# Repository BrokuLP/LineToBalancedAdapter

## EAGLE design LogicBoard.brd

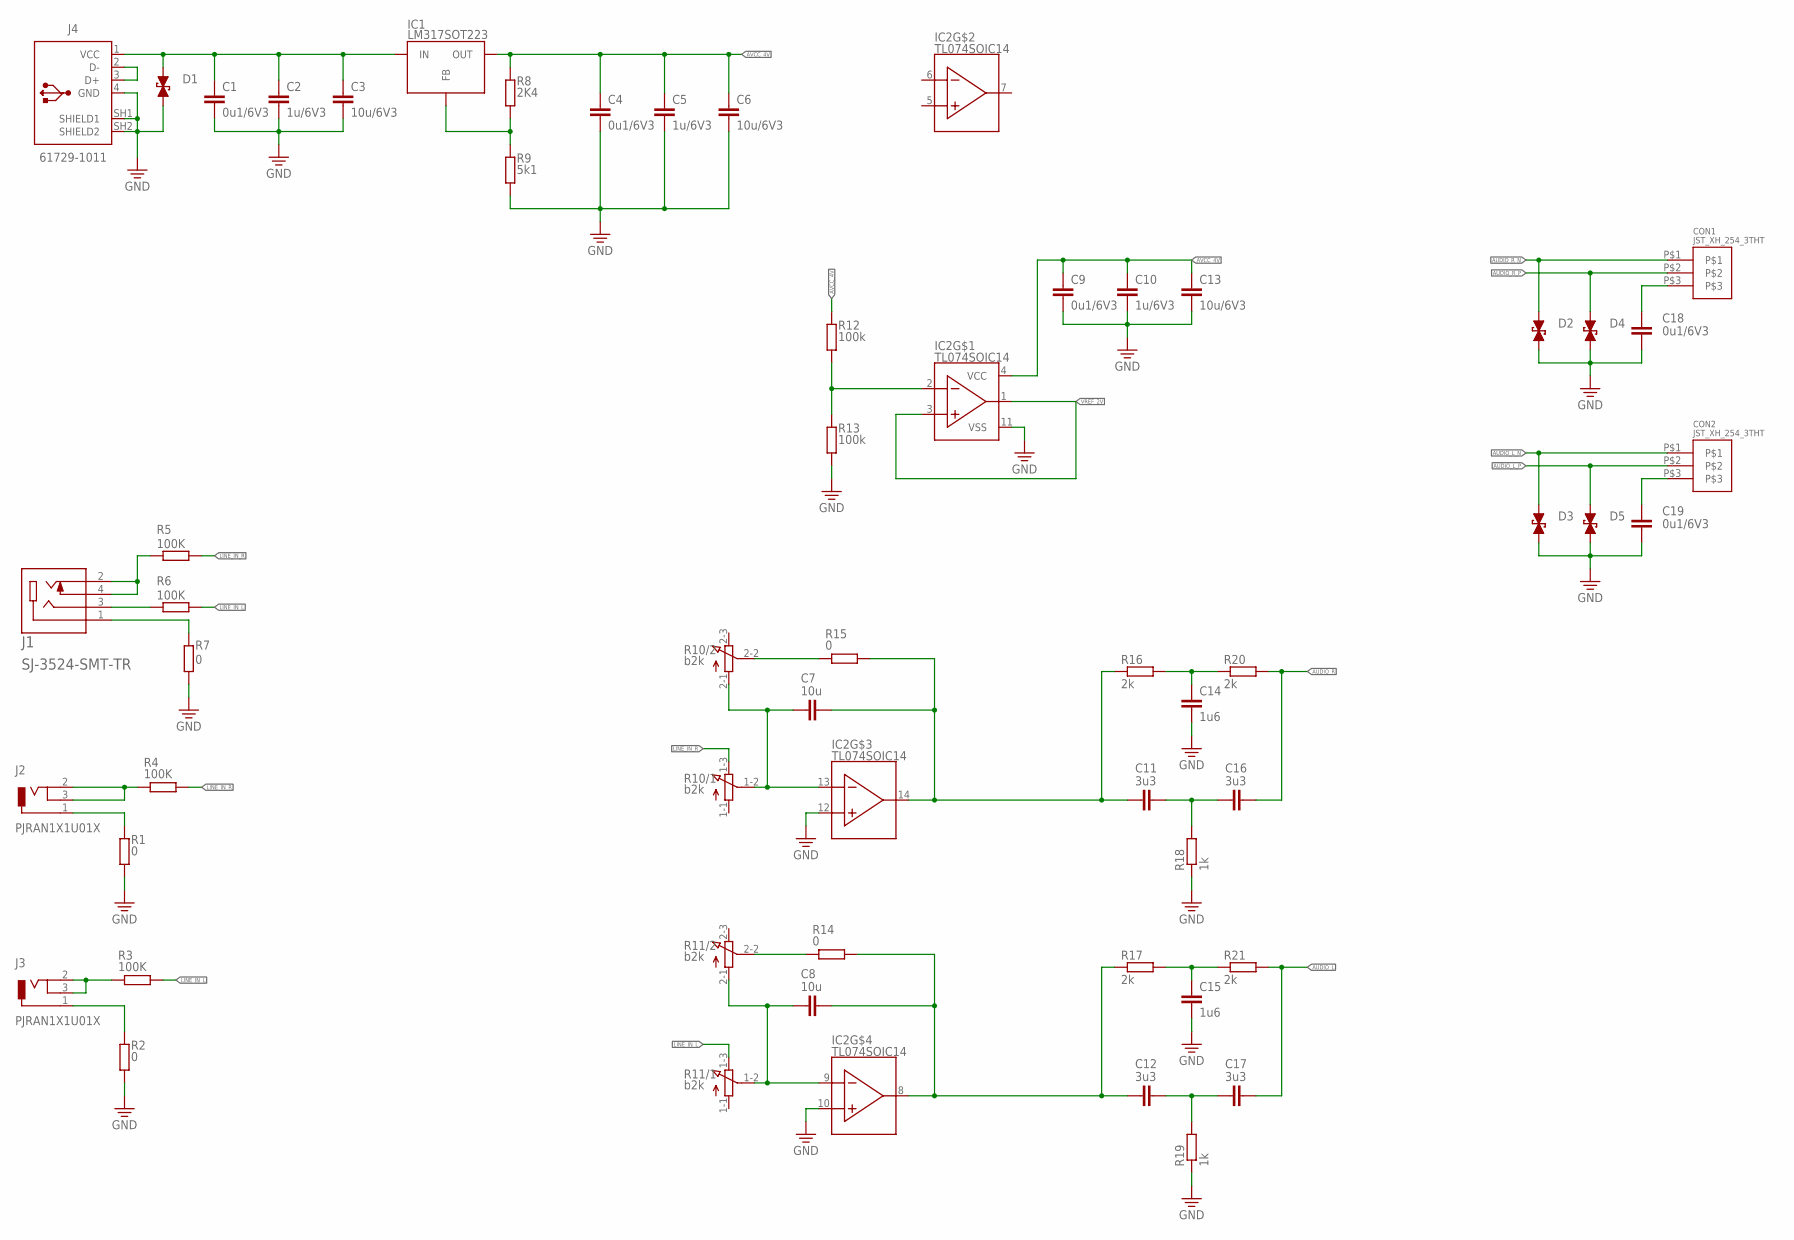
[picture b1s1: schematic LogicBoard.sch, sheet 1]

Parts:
C1, C4, C9, C18, C19: 0u1/6V3; C1206
C2, C5, C10: 1u/6V3; C1206
C3, C6, C13: 10u/6V3; C1206
C7, C8: 10u; C1206
C11, C12, C16, C17: 3u3; C1206
C14, C15: 1u6; C1206
CON1, CON2: JST_XH_254_3THT; JST_XH_254_3_THT
D1, D2, D3, D4, D5: DIODE_PGB-0603MP
IC1: LM317SOT223; SOT230P700X180-4N
IC2: TL074SOIC14; SOIC127P600X175-14N
J1: SJ-3524-SMT-TR
J2, J3: PJRAN1X1U01X
J4: 61729-1011; 61729-1011BLF
R1, R2, R7, R14, R15: 0; R0603
R3, R4, R5, R6: 100K; R0603
R8: 2K4; R0603
R9: 5k1; R0603
R10, R11: b2k; 3RP/1610G
R12, R13: 100k; R0603
R16, R17, R20, R21: 2k; R0603
R18, R19: 1k; R0603

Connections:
AUDIO_L: C17.2, R21.2; also elsewhere on the board
AUDIO_L_N: CON2.P$1, D3.2; also elsewhere on the board
AUDIO_L_P: CON2.P$2, D5.2; also elsewhere on the board
AUDIO_R: C16.2, R20.2; also elsewhere on the board
AUDIO_R_N: CON1.P$1, D2.2; also elsewhere on the board
AUDIO_R_P: CON1.P$2, D4.2; also elsewhere on the board
AVCC_4V: C4.1, C5.1, C6.1, C9.1, C10.1, C13.1, IC1.2 (OUT), IC2.4 (VCC), R8.2, R12.2; also elsewhere on the board
GND: C1.2, C2.2, C3.2, C4.2, C5.2, C6.2, C9.2, C10.2, C13.2, C14.2, C15.2, C18.1, C19.1, D1.1, D2.1, D3.1, D4.1, D5.1, IC2.10 (IN+), IC2.11 (VSS), IC2.12 (IN+), J4.4 (GND), J4.SH1 (SHIELD1), J4.SH2 (SHIELD2), R1.2, R2.2, R7.2, R9.1, R13.1, R18.1, R19.1; also elsewhere on the board
L: J1.3, R6.1
LINE_IN_L: R3.2, R6.2, R11.1-3 (E)
LINE_IN_R: R4.2, R5.2, R10.1-3 (E)
unnamed: C8.1, IC2.9 (IN-), R11.1-2 (S), R11.2-1 (A)
unnamed: C7.1, IC2.13 (IN-), R10.1-2 (S), R10.2-1 (A)
unnamed: C8.2, C12.1, IC2.8 (OUT), R14.2, R17.1
unnamed: C7.2, C11.1, IC2.14 (OUT), R15.2, R16.1
unnamed: C14.1, R16.2, R20.1
unnamed: R10.2-2 (S), R15.1
unnamed: C15.1, R17.2, R21.1
unnamed: C11.2, C16.1, R18.2
unnamed: C12.2, C17.1, R19.2
unnamed: J2.2, J2.3, R4.1
unnamed: J3.2, J3.3, R3.1
unnamed: IC2.2 (IN-), R12.1, R13.2
unnamed: C18.2, CON1.P$3
unnamed: J4.2 (D-), J4.3 (D+)
unnamed: J3.1, R2.1
unnamed: J2.1, R1.1
unnamed: C1.1, C2.1, C3.1, D1.2, IC1.3 (IN), J4.1 (VCC)
unnamed: R11.2-2 (S), R14.1
unnamed: IC1.1 (FB), R8.1, R9.2
unnamed: C19.2, CON2.P$3
R: J1.2, J1.4, R5.1
SCHIRMUNG: J1.1, R7.1
VREF_2V: IC2.1 (OUT), IC2.3 (IN+); also elsewhere on the board

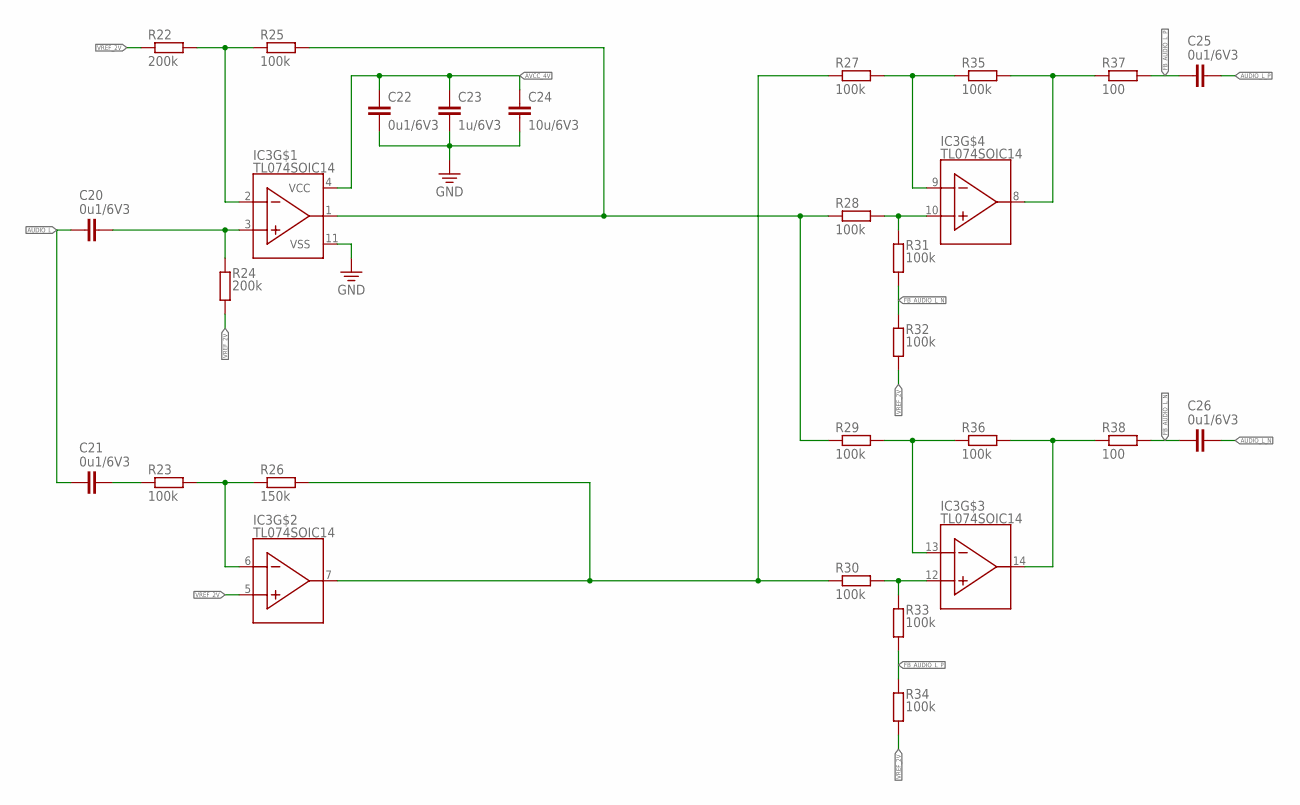
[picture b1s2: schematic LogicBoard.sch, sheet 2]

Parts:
C20, C21, C22, C25, C26: 0u1/6V3; C1206
C23: 1u/6V3; C1206
C24: 10u/6V3; C1206
IC3: TL074SOIC14; SOIC127P600X175-14N
R22, R24: 200k; R0603
R23, R25, R27, R28, R29, R30, R31, R32, R33, R34, R35, R36: 100k; R0603
R26: 150k; R0603
R37, R38: 100; R0603

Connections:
AUDIO_L: C20.2, C21.2; also elsewhere on the board
AUDIO_L_N: C26.1; also elsewhere on the board
AUDIO_L_P: C25.1; also elsewhere on the board
AVCC_4V: C22.1, C23.1, C24.1, IC3.4 (VCC); also elsewhere on the board
FB_AUDIO_L_N: C26.2, R31.2, R32.1, R38.2
FB_AUDIO_L_P: C25.2, R33.2, R34.1, R37.2
GND: C22.2, C23.2, C24.2, IC3.11 (VSS); also elsewhere on the board
unnamed: IC3.6 (IN-), R23.2, R26.1
unnamed: IC3.2 (IN-), R22.2, R25.1
unnamed: IC3.9 (IN-), R27.2, R35.1
unnamed: IC3.8 (OUT), R35.2, R37.1
unnamed: IC3.10 (IN+), R28.2, R31.1
unnamed: IC3.13 (IN-), R29.2, R36.1
unnamed: IC3.14 (OUT), R36.2, R38.1
unnamed: IC3.12 (IN+), R30.2, R33.1
unnamed: IC3.1 (OUT), R25.2, R28.1, R29.1
unnamed: IC3.7 (OUT), R26.2, R27.1, R30.1
unnamed: C20.1, IC3.3 (IN+), R24.2
unnamed: C21.1, R23.1
VREF_2V: IC3.5 (IN+), R22.1, R24.1, R32.2, R34.2; also elsewhere on the board

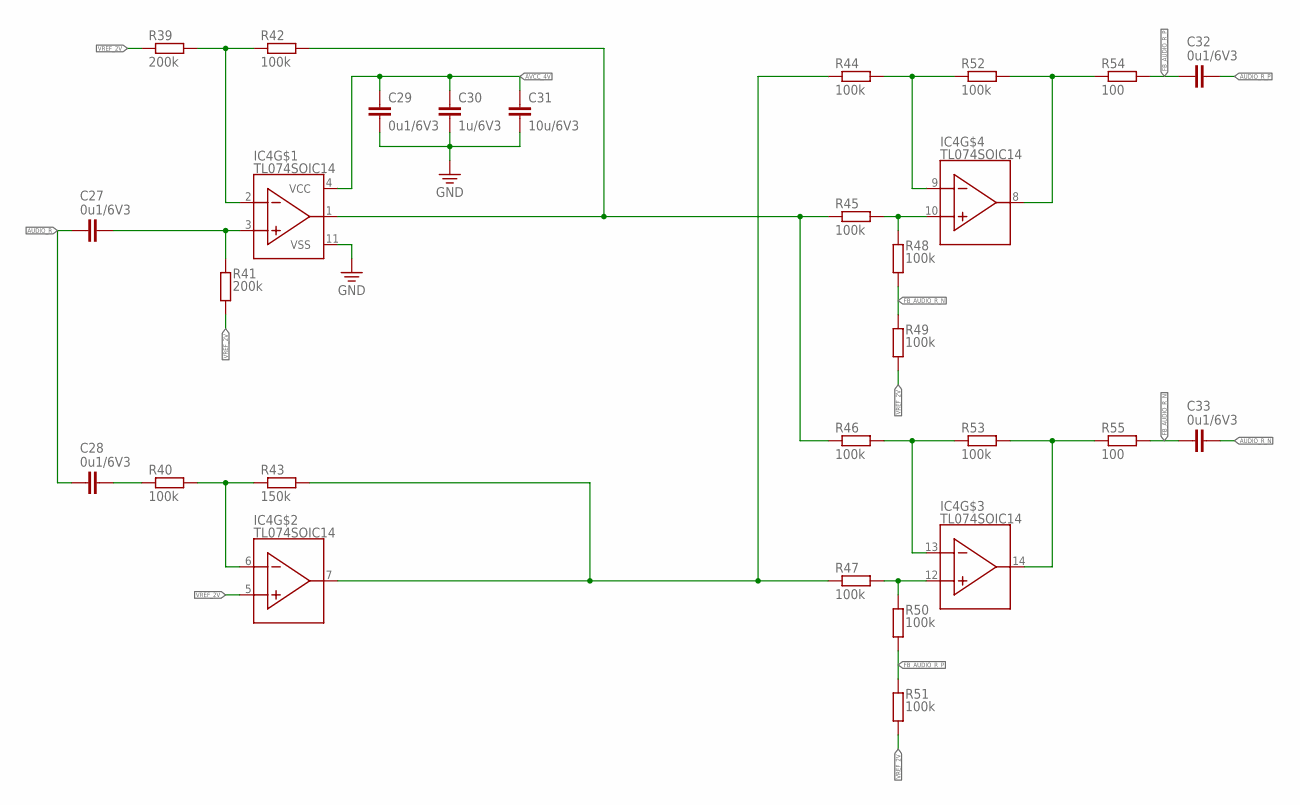
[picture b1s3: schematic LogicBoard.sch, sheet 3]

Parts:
C27, C28, C29, C32, C33: 0u1/6V3; C1206
C30: 1u/6V3; C1206
C31: 10u/6V3; C1206
IC4: TL074SOIC14; SOIC127P600X175-14N
R39, R41: 200k; R0603
R40, R42, R44, R45, R46, R47, R48, R49, R50, R51, R52, R53: 100k; R0603
R43: 150k; R0603
R54, R55: 100; R0603

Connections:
AUDIO_R: C27.2, C28.2; also elsewhere on the board
AUDIO_R_N: C33.1; also elsewhere on the board
AUDIO_R_P: C32.1; also elsewhere on the board
AVCC_4V: C29.1, C30.1, C31.1, IC4.4 (VCC); also elsewhere on the board
FB_AUDIO_R_N: C33.2, R48.2, R49.1, R55.2
FB_AUDIO_R_P: C32.2, R50.2, R51.1, R54.2
GND: C29.2, C30.2, C31.2, IC4.11 (VSS); also elsewhere on the board
unnamed: IC4.6 (IN-), R40.2, R43.1
unnamed: IC4.2 (IN-), R39.2, R42.1
unnamed: IC4.9 (IN-), R44.2, R52.1
unnamed: IC4.8 (OUT), R52.2, R54.1
unnamed: IC4.10 (IN+), R45.2, R48.1
unnamed: IC4.13 (IN-), R46.2, R53.1
unnamed: IC4.14 (OUT), R53.2, R55.1
unnamed: IC4.12 (IN+), R47.2, R50.1
unnamed: IC4.1 (OUT), R42.2, R45.1, R46.1
unnamed: IC4.7 (OUT), R43.2, R44.1, R47.1
unnamed: C27.1, IC4.3 (IN+), R41.2
unnamed: C28.1, R40.1
VREF_2V: IC4.5 (IN+), R39.1, R41.1, R49.2, R51.2; also elsewhere on the board

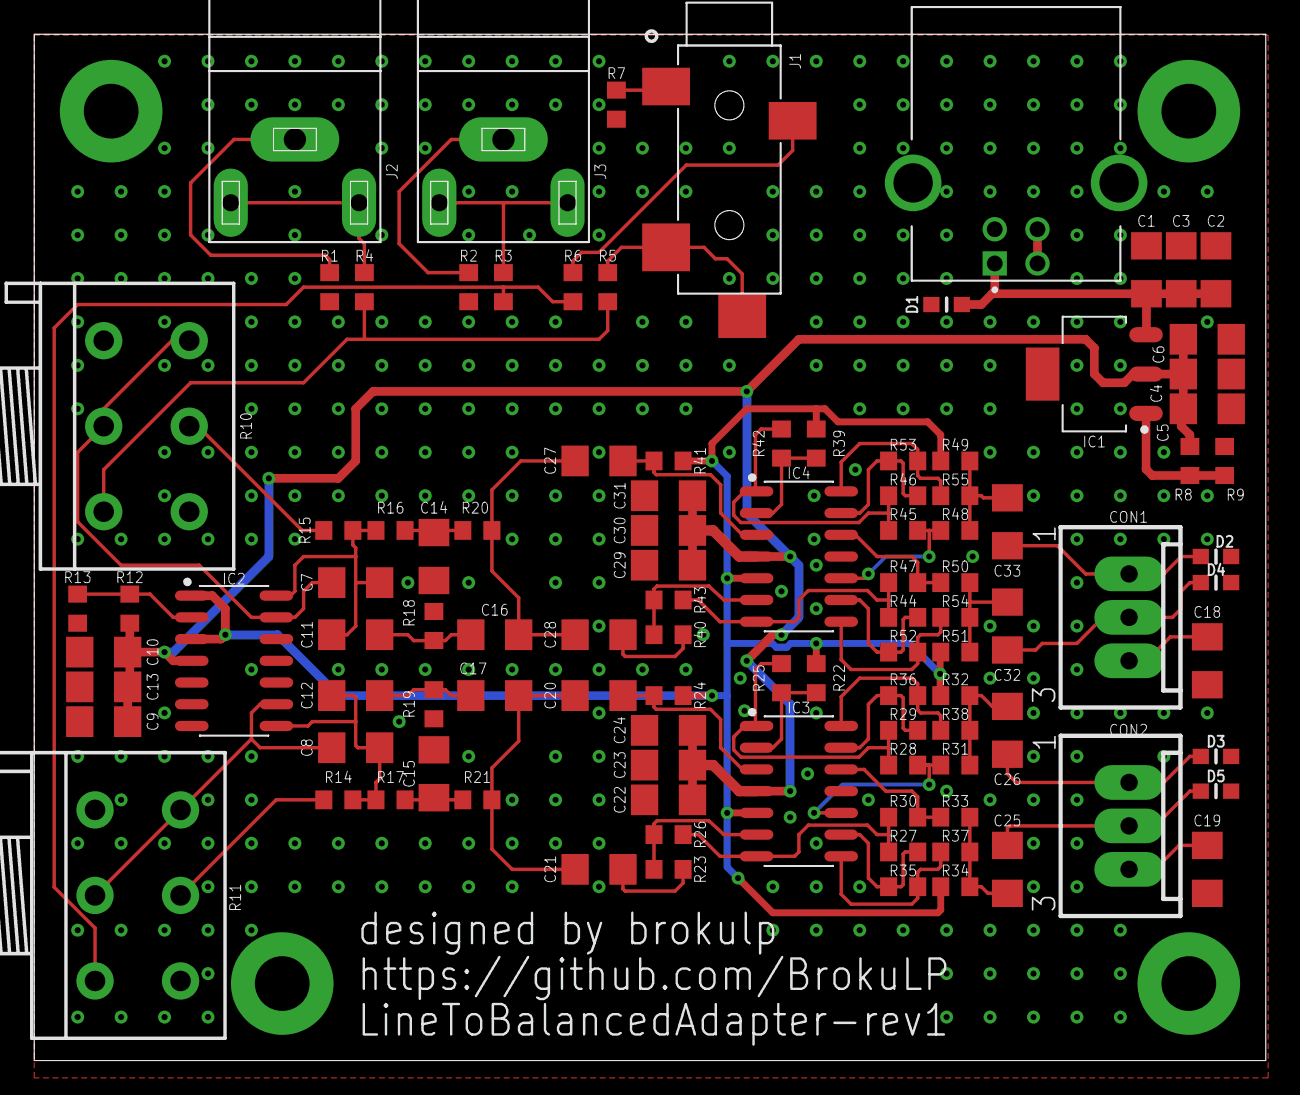
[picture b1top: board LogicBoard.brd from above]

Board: 2 copper layers, 71.9 x 60.0 mm, 103 parts (0 on the bottom side), 62 nets.

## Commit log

2022-12-09 inital commit
2022-12-09 shematic finished
2022-12-09 rev1 complete - DRC runs without errors
2022-12-09 added step model - renamed gerber files
